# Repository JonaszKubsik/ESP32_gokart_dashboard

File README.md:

https://github.com/user-attachments/assets/68bce8ad-3ff0-40eb-8be3-2b12850ca796

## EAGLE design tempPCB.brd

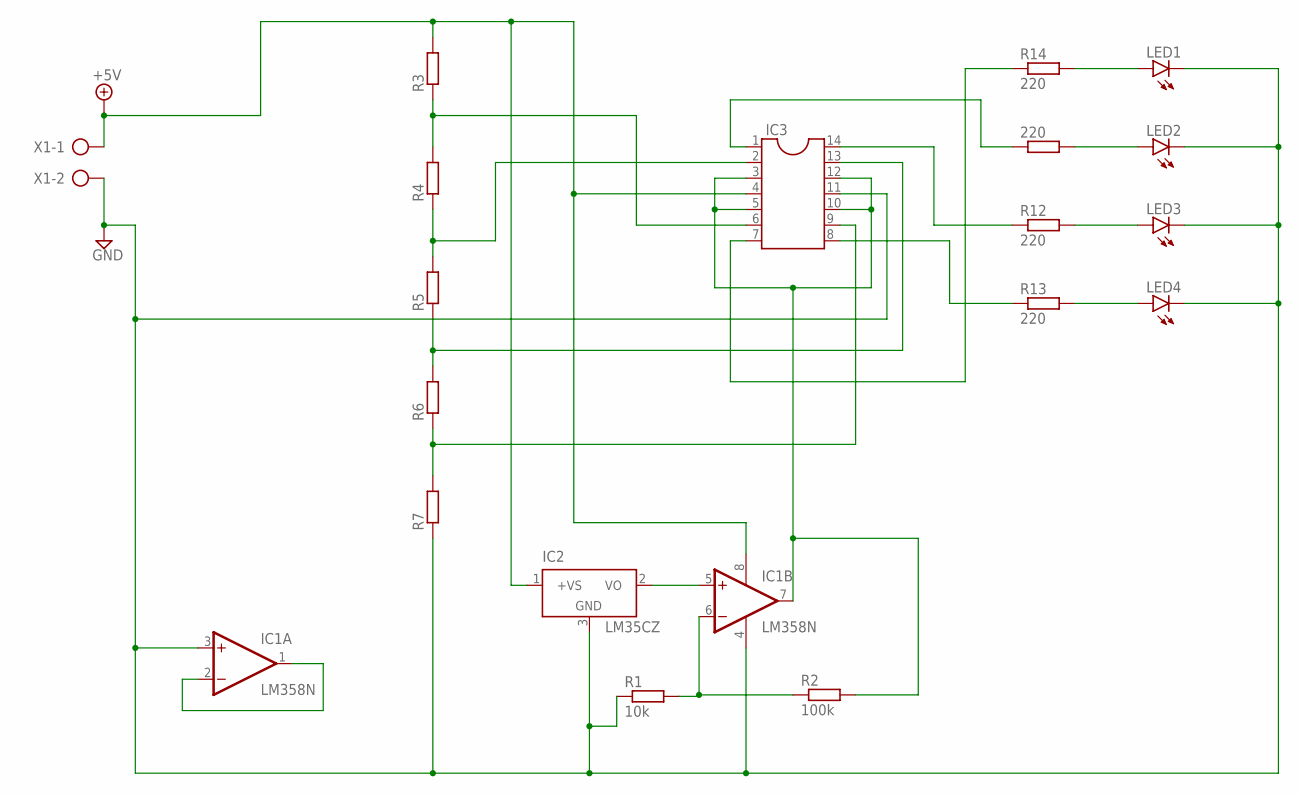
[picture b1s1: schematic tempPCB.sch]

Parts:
220: R-EU_0207/10; 0207/10
IC1: LM358N; DIL08
IC2: LM35CZ; TO92
IC3: DIL14
LED1, LED2, LED3, LED4: LED5MM
R1: 10k; R1206
R2: 100k; R1206
R3, R5, R7: R-EU_R1206; R1206
R4, R6: R-EU_0207/10; 0207/10
R12, R13, R14: 220; 0207/10
X1: AK500/2

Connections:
+5V: IC1.8 (V+), IC2.1 (+VS), IC3.4, R3.2, X1.1
GND: IC1.3 (+IN), IC1.4 (V-), IC2.3 (GND), IC3.11, LED1.K (C), LED2.K (C), LED3.K (C), LED4.K (C), R1.1, R7.1, X1.2
unnamed: LED1.A, R14.2
unnamed: 220.2, LED2.A
unnamed: LED3.A, R12.2
unnamed: LED4.A, R13.2
unnamed: IC1.1 (OUT), IC1.2 (-IN)
unnamed: IC3.7, R14.1
unnamed: 220.1, IC3.1
unnamed: IC3.14, R12.1
unnamed: IC3.8, R13.1
unnamed: IC3.13, R5.1, R6.2
unnamed: IC1.5 (+IN), IC2.2 (VO)
unnamed: IC1.6 (-IN), R1.2, R2.1
unnamed: IC1.7 (OUT), IC3.3, IC3.5, IC3.10, IC3.12, R2.2
unnamed: IC3.9, R6.1, R7.2
unnamed: IC3.2, R4.1, R5.2
unnamed: IC3.6, R3.1, R4.2

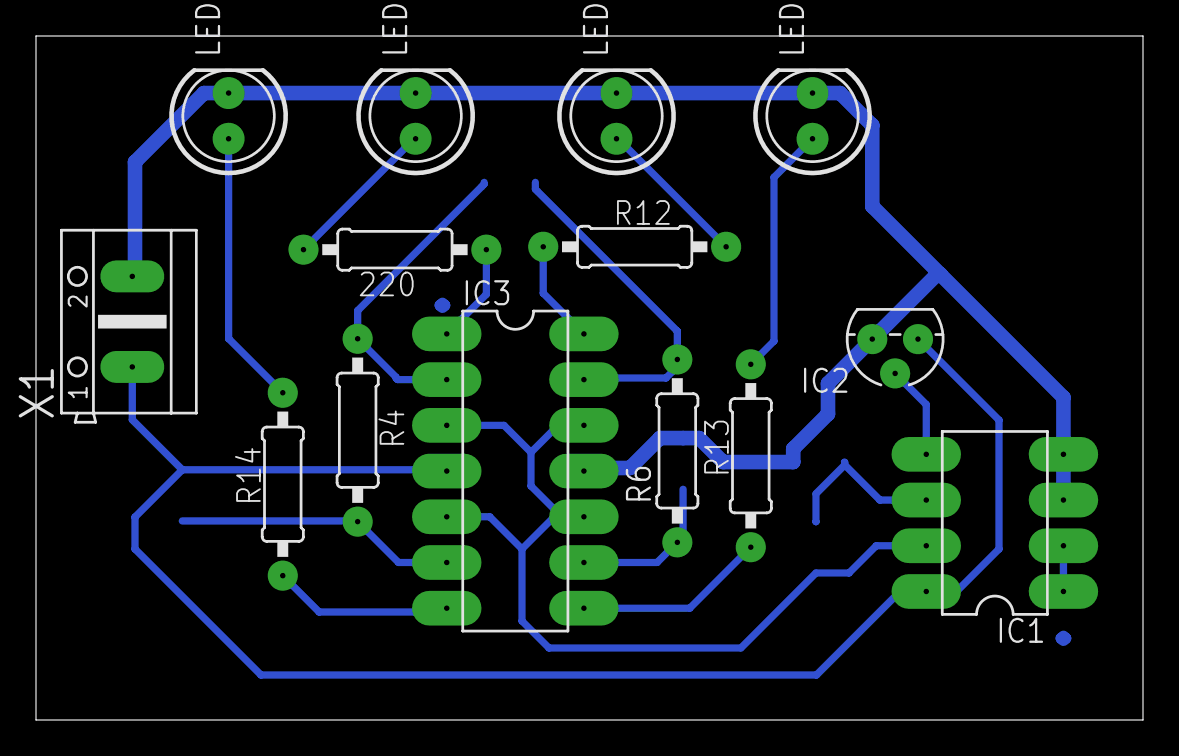
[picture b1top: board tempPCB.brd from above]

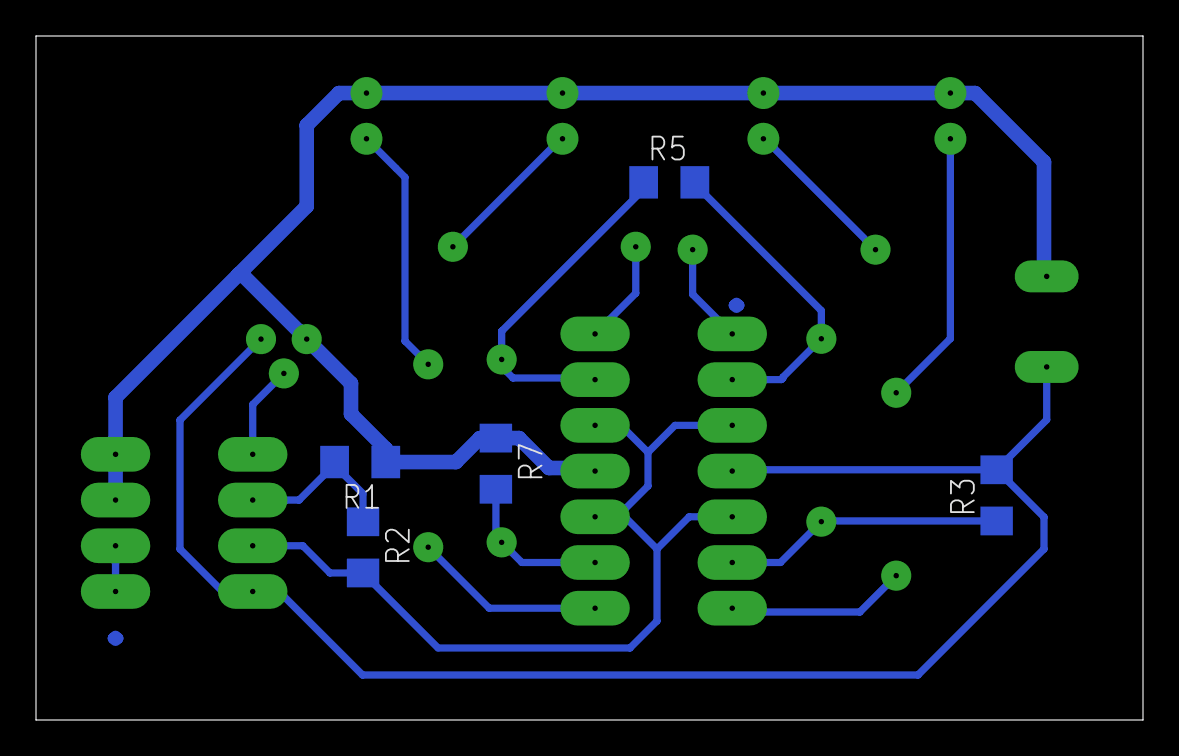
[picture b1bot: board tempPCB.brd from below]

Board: 2 copper layers, 61.5 x 38.0 mm, 19 parts (5 on the bottom side), 18 nets.

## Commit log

2026-04-27 GPS finally working and first iteration of LCD
2026-04-27 Add temp sensor on one wire
2026-05-27 Analog thermometer LM35 (board + simulation)
2026-05-27 Create PCB folder
2026-05-27 Move board to PCB folder
2026-05-27 Move simulation to PCB folder
2026-06-02 Rename PCB/IMG_8573.jpeg to PCB/photos/top.jpeg
    Create photos folder
2026-06-02 Rename PCB/IMG_8574.jpeg to PCB/photos/bot.jpeg
    Add PCB bottom photo
2026-06-23 Update display overlay
